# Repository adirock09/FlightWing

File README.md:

# FlightWing

I made a custom Flight Controller which controls 3 Servos and 1 Escs which is based on an STM32 chip , it has 6 channel input available so it can be connected to a receiver and has a microSD Card, battery charger , IMU and Pressure Sensor . It has a USB-C for uploading code and charging purpose.

## Features

- Based on STM32 Chip
- 2-layer compact PCB
- USB connection for programming and power
- Onboard 3.3V and 5V voltage regulation
- Compact footprint for small projects
- IMU and Pressure Sensor<br>
- 
- ## Bill of Materials (BOM)
| Serial Num | Description | Total (USD) | 
|----:|--------------------------|-------------|
| 1  | PCB and Assembly  |77.86 |
| 2 | Shipping JLCPCB  |14.51 |

<br>
### 💰 Cost Summary

- **Estimated Total Cost ( PCB ASSEMBLY + Shipping):** **$92.37	 USD**
-  ## Schematic & PCB<br>
<br>
<br>

## 3d Render<br>
<br>
<br>

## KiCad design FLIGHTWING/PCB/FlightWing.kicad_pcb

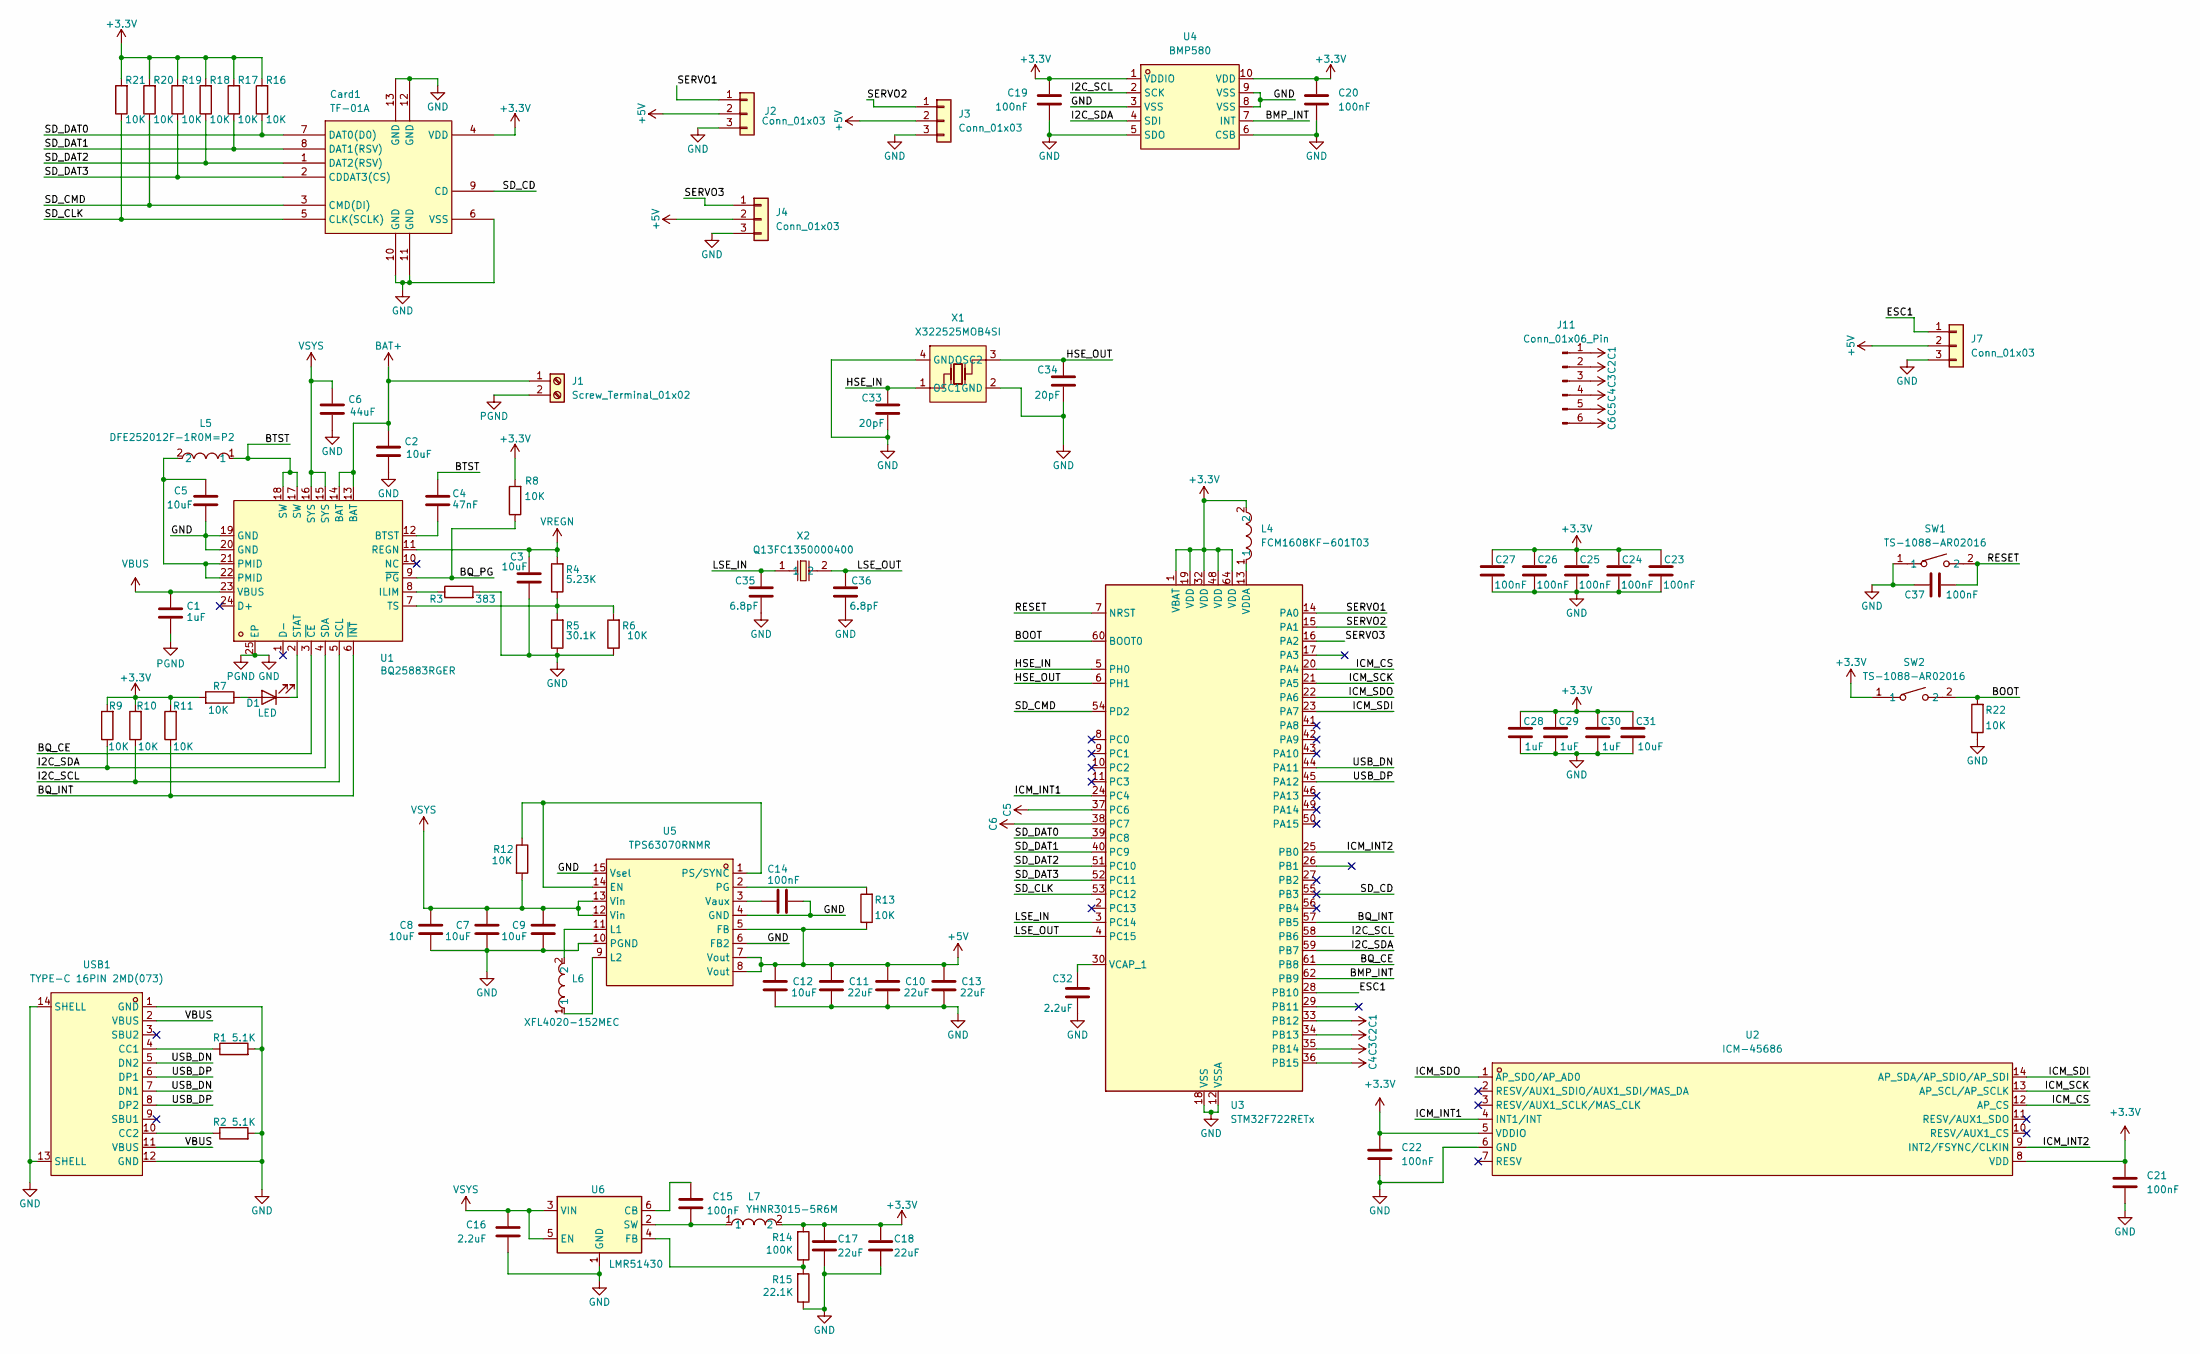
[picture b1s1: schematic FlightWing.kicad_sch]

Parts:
C1, C28, C29, C30: 1uF; C_0402_1005Metric
C2, C9, C12: 10uF; C_0603_1608Metric
C3, C5, C31: 10uF; C_0402_1005Metric
C4: 47nF; C_0201_0603Metric
C6: 44uF; C_0603_1608Metric
C7, C8: 10uF; C_0805_2012Metric
C10, C11, C13: 22uF; C_0805_2012Metric
C14, C15, C19, C20, C21, C22, C23, C24, C25, C26, C27, C37: 100nF; C_0201_0603Metric
C16: 2.2uF; C_0603_1608Metric
C17, C18: 22uF; C_0402_1005Metric
C32: 2.2uF; C_0201_0603Metric
C33, C34: 20pF; C_0201_0603Metric
C35, C36: 6.8pF; C_0201_0603Metric
Card1: TF-01A; TF-SMD_TF-01A; LCSC Part C91145
D1: LED; LED_0402_1005Metric
J1: Screw_Terminal_01x02; TerminalBlock_Xinya_XY308-2.54-2P_1x02_P2.54mm_Horizontal
J2, J3, J4, J7: Conn_01x03; PinHeader_1x03_P2.54mm_Vertical
J11: Conn_01x06_Pin; PinHeader_1x06_P2.54mm_Vertical
L4: FCM1608KF-601T03; L0603; LCSC Part C141723
L5: DFE252012F-1R0M=P2; L2520; LCSC Part C435392
L6: XFL4020-152MEC; IND-SMD_L4.0-W4.0-A; LCSC Part C3033018
L7: YHNR3015-5R6M; IND-SMD_L3.0-W3.0; LCSC Part C18236327
R1, R2: 5.1K; R_0201_0603Metric
R3: 383; R_0201_0603Metric
R4: 5.23K; R_0201_0603Metric
R5: 30.1K; R_0201_0603Metric
R6, R7, R8, R9, R10, R11, R12, R13, R16, R17, R18, R19, R20, R21, R22: 10K; R_0201_0603Metric
R14: 100K; R_0402_1005Metric
R15: 22.1K; R_0402_1005Metric
SW1, SW2: TS-1088-AR02016; SW-SMD_L3.9-W3.0-P4.45; LCSC Part C720477
U1: BQ25883RGER; VFQFPN-24_L4.0-W4.0-P0.50-BL-EP2.8; LCSC Part C544362
U2: ICM-45686; LGA-14_L3.0-W2.5-P0.50-TL; LCSC Part C22459454
U3: STM32F722RETx; LQFP-64_10x10mm_P0.5mm
U4: BMP580; LGA-10_L2.0-W2.0-P0.50-TL_BMP580; LCSC Part C22391138
U5: TPS63070RNMR; VQFN-HR-15_L3.0-W2.5-P0.50-BL_TPS63070RNMR; LCSC Part C109322
U6: LMR51430; SOT-23-6
USB1: TYPE-C 16PIN 2MD(073); USB-C-SMD_TYPE-C-6PIN-2MD-073; LCSC Part C2765186
X1: X322525MOB4SI; CRYSTAL-SMD_4P-L3.2-W2.5-BL; LCSC Part C9006
X2: Q13FC1350000400; FC-135R_L3.2-W1.5; LCSC Part C32346

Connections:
+3.3V: C17.1, C18.1, C19.1, C20.1, C21.1, C22.1, C23.1, C24.1, C25.1, C26.1, C27.1, C28.1, C29.1, C30.1, C31.1, Card1.4 (VDD), L4.2, L7.2, R7.2, R8.2, R9.2, R10.2, R11.2, R14.2, R16.2, R17.2, R18.2, R19.2, R20.2, R21.2, SW2.1, U2.5 (VDDIO), U2.8 (VDD), U3.1 (VBAT), U3.19 (VDD), U3.32 (VDD), U3.48 (VDD), U3.64 (VDD), U4.1 (VDDIO), U4.10 (VDD)
+5V: C10.1, C11.1, C12.1, C13.1, J2.2, J3.2, J4.2, J7.2, R13.1, U5.5 (FB), U5.7 (Vout), U5.8 (Vout)
/BMP_INT: U3.62 (PB9), U4.7 (INT)
/BOOT: R22.2, SW2.2, U3.60 (BOOT0)
/BQ_CE: U1.3 (~CE), U3.61 (PB8)
/BQ_INT: R11.1, U1.6 (~INT), U3.57 (PB5)
/BQ_PG: R8.1, U1.9 (~PG)
/BTST: C4.1, L5.1, U1.17 (SW), U1.18 (SW)
/ESC1: J7.1, U3.28 (PB10)
/HSE_IN: C33.1, U3.5 (PH0), X1.1 (OSC1)
/HSE_OUT: C34.1, U3.6 (PH1), X1.3 (OSC2)
/I2C_SCL: R10.1, U1.5 (SCL), U3.58 (PB6), U4.2 (SCK)
/I2C_SDA: R9.1, U1.4 (SDA), U3.59 (PB7), U4.4 (SDI)
/ICM_CS: U2.12 (AP_CS), U3.20 (PA4)
/ICM_INT1: U2.4 (INT1/INT), U3.24 (PC4)
/ICM_INT2: U2.9 (INT2/FSYNC/CLKIN), U3.25 (PB0)
/ICM_SCK: U2.13 (AP_SCL/AP_SCLK), U3.21 (PA5)
/ICM_SDI: U2.14 (AP_SDA/AP_SDIO/AP_SDI), U3.23 (PA7)
/ICM_SDO: U2.1 (AP_SDO/AP_AD0), U3.22 (PA6)
/LSE_IN: C35.1, U3.3 (PC14), X2.1
/LSE_OUT: C36.1, U3.4 (PC15), X2.2
/RESET: C37.2, SW1.2, U3.7 (NRST)
/SD_CD: Card1.9 (CD), U3.55 (PB3)
/SD_CLK: Card1.5 (CLK(SCLK)), R21.1, U3.53 (PC12)
/SD_CMD: Card1.3 (CMD(DI)), R20.1, U3.54 (PD2)
/SD_DAT0: Card1.7 (DAT0(D0)), R16.1, U3.39 (PC8)
/SD_DAT1: Card1.8 (DAT1(RSV)), R17.1, U3.40 (PC9)
/SD_DAT2: Card1.1 (DAT2(RSV)), R18.1, U3.51 (PC10)
/SD_DAT3: Card1.2 (CDDAT3(CS)), R19.1, U3.52 (PC11)
/SERVO1: J2.1, U3.14 (PA0)
/SERVO2: J3.1, U3.15 (PA1)
/SERVO3: J4.1, U3.16 (PA2)
/USB_DN: U3.44 (PA11), USB1.5 (DN2), USB1.7 (DN1)
/USB_DP: U3.45 (PA12), USB1.6 (DP1), USB1.8 (DP2)
BAT+: C2.1, J1.1, U1.13 (BAT), U1.14 (BAT)
C1: J11.1, U3.33 (PB12)
C2: J11.2, U3.34 (PB13)
C3: J11.3, U3.35 (PB14)
C4: J11.4, U3.36 (PB15)
C5: J11.5, U3.37 (PC6)
C6: J11.6, U3.38 (PC7)
GND: C1.2, C2.2, C3.2, C5.2, C6.2, C7.2, C8.2, C9.2, C10.2, C11.2, C12.2, C13.2, C14.2, C16.2, C17.2, C18.2, C19.2, C20.2, C21.2, C22.2, C23.2, C24.2, C25.2, C26.2, C27.2, C28.2, C29.2, C30.2, C31.2, C32.2, C33.2, C34.2, C35.2, C36.2, C37.1, Card1.6 (VSS), Card1.10 (GND), Card1.11 (GND), Card1.12 (GND), Card1.13 (GND), J1.2, J2.3, J3.3, J4.3, J7.3, R1.2, R2.2, R3.2, R5.1, R6.1, R15.1, R22.1, SW1.1, U1.19 (GND), U1.20 (GND), U1.25 (EP), U2.6 (GND), U3.12 (VSSA), U3.18 (VSS), U3.31 (VSS), U3.47 (VSS), U3.63 (VSS), U4.3 (VSS), U4.5 (SDO), U4.6 (CSB), U4.8 (VSS), U4.9 (VSS), U5.4 (GND), U5.6 (FB2), U5.10 (PGND), U5.15 (Vsel), U6.1 (GND), USB1.1 (GND), USB1.12 (GND), USB1.13 (SHELL), USB1.14 (SHELL), X1.2 (GND), X1.4 (GND)
unnamed: C5.1, L5.2, U1.21 (PMID), U1.22 (PMID)
unnamed: D1.2 (A), R7.1
unnamed: D1.1 (K), U1.2 (STAT)
unnamed: C4.2, U1.12 (BTST)
unnamed: R3.1, U1.8 (ILIM)
unnamed: R4.1, R5.2, R6.2, U1.7 (TS)
unnamed: C32.1, U3.30 (VCAP_1)
unnamed: L4.1, U3.13 (VDDA)
unnamed: R12.1, U5.1 (PS/SYNC), U5.14 (EN)
unnamed: L6.2, U5.11 (L1)
unnamed: L6.1, U5.9 (L2)
unnamed: R13.2, U5.2 (PG)
unnamed: C14.1, U5.3 (Vaux)
unnamed: C15.1, U6.6 (CB)
unnamed: R14.1, R15.2, U6.4 (FB)
unnamed: C15.2, L7.1, U6.2 (SW)
unnamed: R1.1, USB1.4 (CC1)
unnamed: R2.1, USB1.10 (CC2)
VBUS: C1.1, U1.23 (VBUS), USB1.2 (VBUS), USB1.11 (VBUS)
VREGN: C3.1, R4.2, U1.11 (REGN)
VSYS: C6.1, C7.1, C8.1, C9.1, C16.1, R12.2, U1.15 (SYS), U1.16 (SYS), U5.12 (Vin), U5.13 (Vin), U6.3 (VIN), U6.5 (EN)

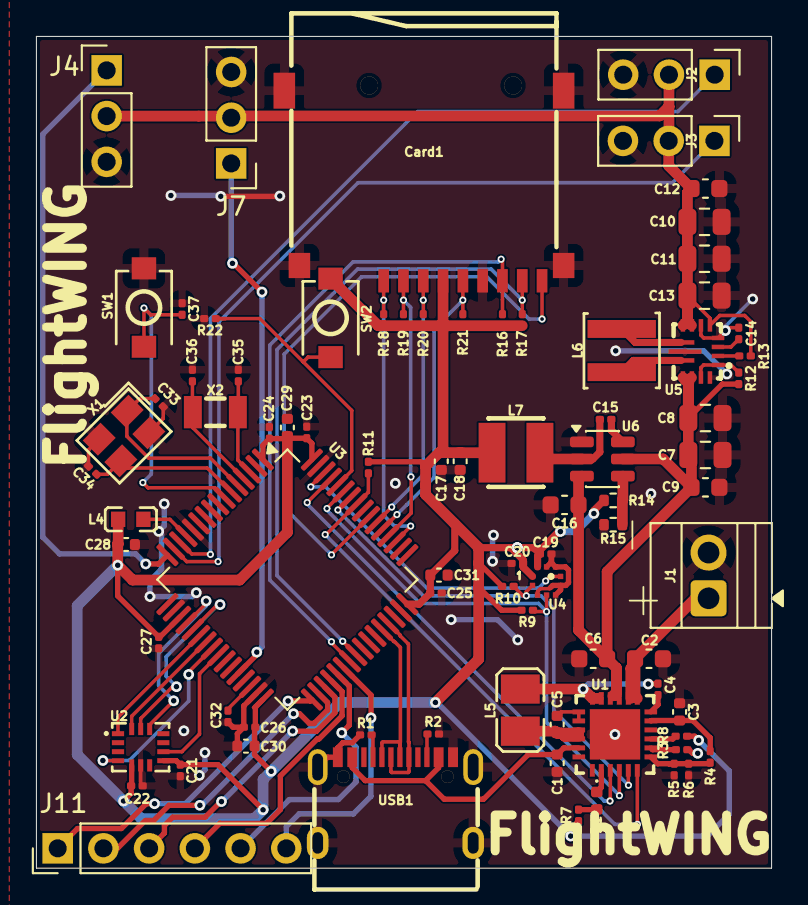
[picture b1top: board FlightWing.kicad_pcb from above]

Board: 2 copper layers, 40.8 x 46.2 mm, 82 parts (0 on the bottom side), 63 nets.

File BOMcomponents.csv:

Designator,Footprint,Quantity,Value,LCSC Part #
"BOOT, RESET",SW-SMD_L3.9-W3.0-P4.45,2,TS-1088-AR02016,C720477
"C1, C28, C29, C30",0402,4,1uF,
"C10, C11, C13",0805,3,22uF,
"C12, C2, C9",0603,3,10uF,
"C14, C15, C19, C20, C21, C22, C23, C24, C25, C26, C27, C37",0201,12,100nF,
C16,0603,1,2.2uF,
"C17, C18",0402,2,22uF,
"C3, C31, C5",0402,3,10uF,
C32,0201,1,2.2uF,
"C33, C34, C35, C36",0201,4,20pF,
C4,0201,1,47nF,
C6,0603,1,44uF,
"C7, C8",0805,2,10uF,
CARD1,TF-SMD_TF-01A,1,TF-01A,C91145
D1,0402,1,LED,
J1,TerminalBlock_Xinya_XY308-2.54-2P_1x02_P2.54mm_Horizontal,1,Screw_Terminal_01x02,
"J2, J3",PinHeader_1x03_P2.54mm_Vertical,2,Conn_01x03,
L4,L0603,1,FCM1608KF-601T03,C141723
L5,L2520,1,DFE252012F-1R0M=P2,C435392
L6,IND-SMD_L4.0-W4.0-A,1,XFL4020-152MEC,C3033018
L7,IND-SMD_L3.0-W3.0,1,YHNR3015-5R6M,C18236327
"R1, R2",0201,2,5.1K,
"R10, R11, R12, R13, R16, R17, R18, R19, R20, R21, R22, R6, R7, R8, R9",0201,15,10K,
R14,0402,1,100K,
R15,0402,1,22.1K,
R3,0201,1,383,
R4,0201,1,5.23K,
R5,0201,1,30.1K,
U1,VFQFPN-24_L4.0-W4.0-P0.50-BL-EP2.8,1,BQ25883RGER,C544362
U2,LGA-14_L3.0-W2.5-P0.50-TL,1,ICM-45686,C22459454
U3,LQFP-64_10x10mm_P0.5mm,1,STM32F722RETx,
U4,LGA-10_L2.0-W2.0-P0.50-TL_BMP580,1,BMP580,C22391138
U5,VQFN-HR-15_L3.0-W2.5-P0.50-BL_TPS63070RNMR,1,TPS63070RNMR,C109322
U6,SOT-23-6,1,LMR51430,
USB1,USB-C-SMD_TYPE-C-6PIN-2MD-073,1,TYPE-C 16PIN 2MD(073),C2765186
X1,CRYSTAL-SMD_4P-L3.2-W2.5-BL,1,X322525MOB4SI,C9006
X2,FC-135R_L3.2-W1.5,1,Q13FC1350000400,C32346

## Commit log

2026-03-05 Rename Screenshot (203).png to options for PCBA
2026-03-05 Rename options for PCBA to options for PCBA.png
